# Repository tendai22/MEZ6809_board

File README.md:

# MEZ6809_board ... Mezzanine board of MC/HD6809 for EMUPU_RAM48

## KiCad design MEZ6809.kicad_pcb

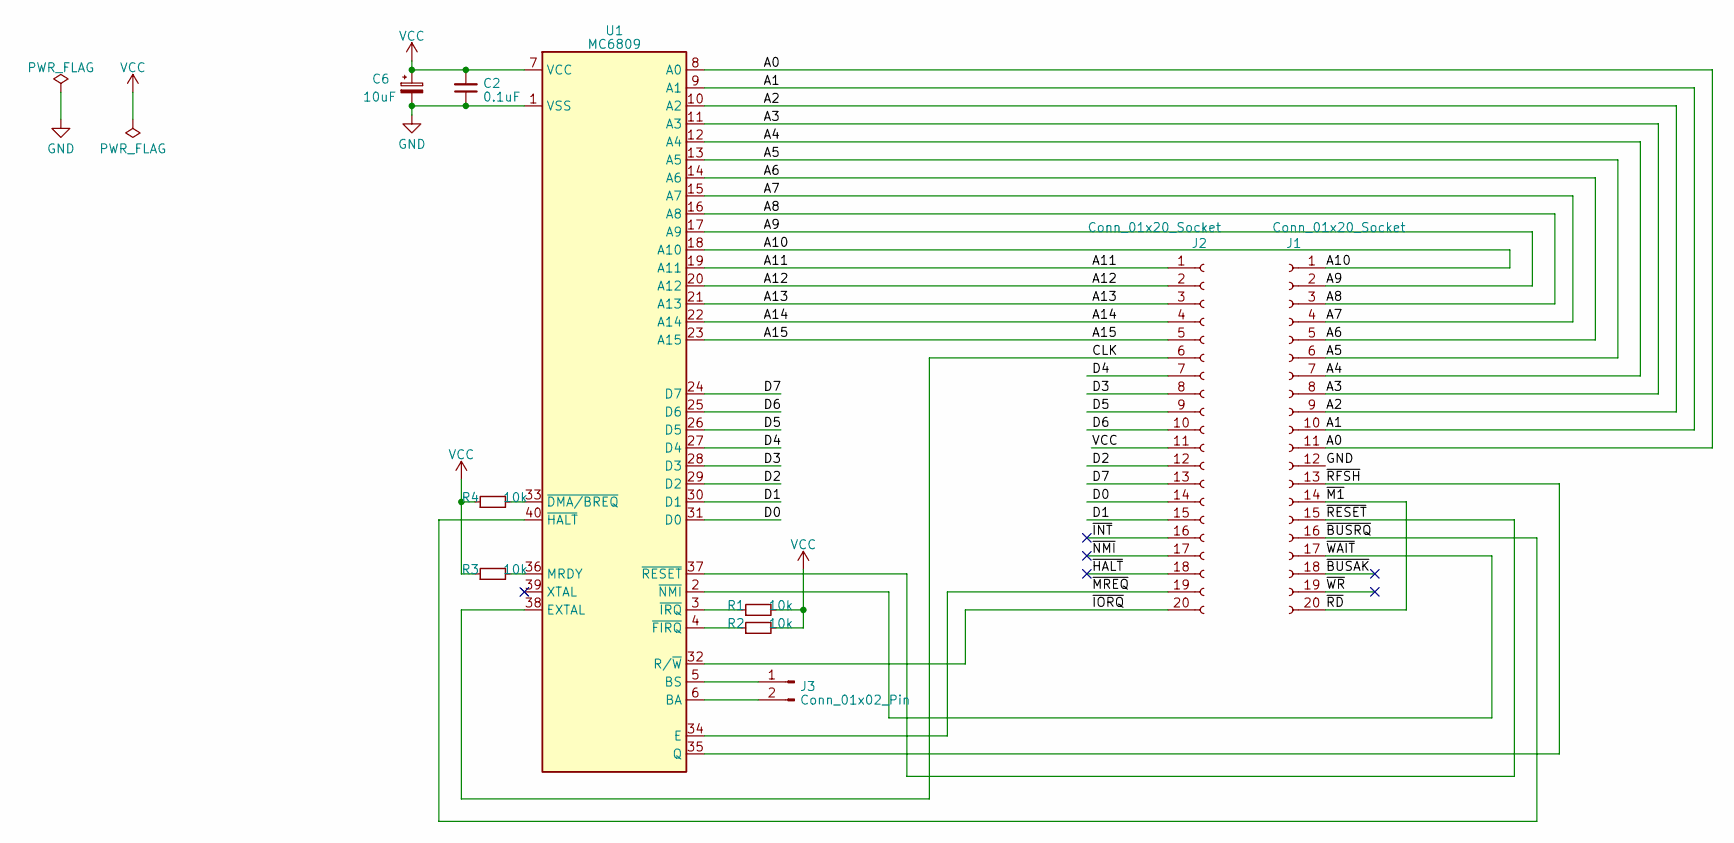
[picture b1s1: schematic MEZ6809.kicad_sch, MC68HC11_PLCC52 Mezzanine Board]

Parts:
C2: 0.1uF; C_Disc_D3.0mm_W1.6mm_P2.50mm
C6: 10uF; CP_Radial_D4.0mm_P2.00mm
J1, J2: Conn_01x20_Socket; PinSocket_1x20_P2.54mm_Vertical
J3: Conn_01x02_Pin; PinSocket_1x02_P2.54mm_Vertical
R1, R2, R3, R4: 10k; R_Axial_DIN0204_L3.6mm_D1.6mm_P7.62mm_Horizontal
U1: MC6809; DIP-40_W15.24mm

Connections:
/A0: J1.11, U1.8 (A0)
/A1: J1.10, U1.9 (A1)
/A2: J1.9, U1.10 (A2)
/A3: J1.8, U1.11 (A3)
/A4: J1.7, U1.12 (A4)
/A5: J1.6, U1.13 (A5)
/A6: J1.5, U1.14 (A6)
/A7: J1.4, U1.15 (A7)
/A8: J1.3, U1.16 (A8)
/A9: J1.2, U1.17 (A9)
/A10: J1.1, U1.18 (A10)
/A11: J2.1, U1.19 (A11)
/A12: J2.2, U1.20 (A12)
/A13: J2.3, U1.21 (A13)
/A14: J2.4, U1.22 (A14)
/A15: J2.5, U1.23 (A15)
/CLK: J2.6, U1.38 (EXTAL)
/D0: J2.14, U1.31 (D0)
/D1: J2.15, U1.30 (D1)
/D2: J2.12, U1.29 (D2)
/D3: J2.8, U1.28 (D3)
/D4: J2.7, U1.27 (D4)
/D5: J2.9, U1.26 (D5)
/D6: J2.10, U1.25 (D6)
/D7: J2.13, U1.24 (D7)
/~BUSAK: J1.18
/~BUSRQ: J1.16, U1.40 (~HALT)
/~HALT: J2.18
/~INT: J2.16
/~IORQ: J2.20, U1.32 (R/~W)
/~M1: J1.14, J1.20
/~MREQ: J2.19, U1.34 (E)
/~NMI: J2.17
/~RESET: J1.15, U1.37 (~RESET)
/~RFSH: J1.13, U1.35 (Q)
/~WAIT: J1.17, U1.2 (~NMI)
/~WR: J1.19
GND: C2.1, C6.2, J1.12, U1.1 (VSS)
unnamed: J3.1, U1.5 (BS)
unnamed: J3.2, U1.6 (BA)
unnamed: R3.2, U1.36 (MRDY)
unnamed: R4.2, U1.33 (~DMA/BREQ)
unnamed: R2.1, U1.4 (~FIRQ)
unnamed: R1.1, U1.3 (~IRQ)
VCC: C2.2, C6.1, J2.11, R1.2, R2.2, R3.1, R4.1, U1.7 (VCC)

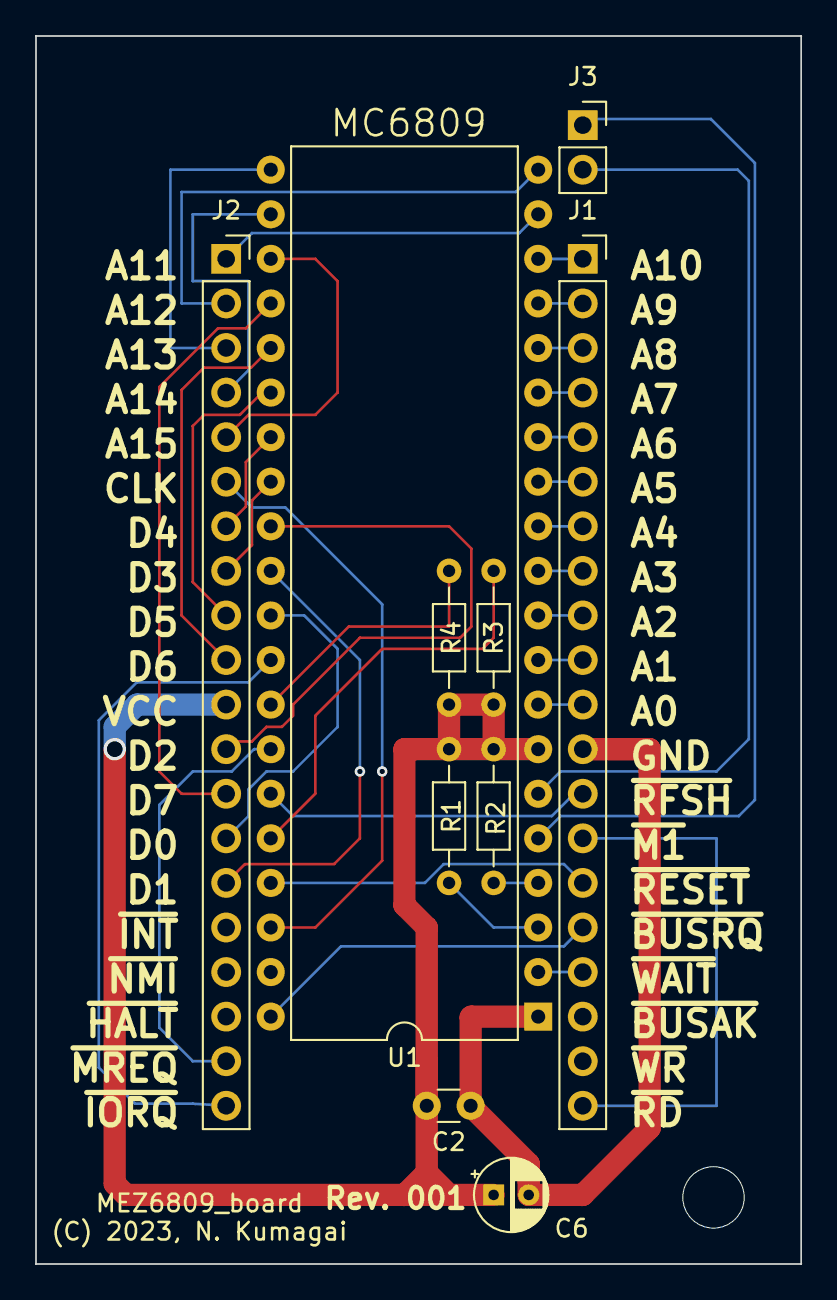
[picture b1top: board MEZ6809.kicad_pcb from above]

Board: 2 copper layers, 43.6 x 70.0 mm, 11 parts (0 on the bottom side), 40 nets.

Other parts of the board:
H4: MountingHole; MountingHole_3.5mm

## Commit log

2023-09-19 initial commit, and Rev001

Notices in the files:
MEZ6809.kicad_pcb:
(C) 2023, N. Kumagai
